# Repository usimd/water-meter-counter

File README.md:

# Inductive water meter counter with S0 interface for GSB-8 meters

This is a custom water meter counter project to get an interface to analog water meter readings
for subsequent usage in Homeassistant. The project is outputting its readings via a generic S0
interface, though, to enable other use cases as well.

It features a custom 3D-printable model to snap on to the GSB-8 meter that houses the PCB. The
software doing the actual work is located in the [`firmware`](./firmware) folder. Since it is
based on a Microchip PIC controller, it requires the respective infrastructure to build.

Bundled assets are available as GitHub releases, created by CI for every `v*` tag:

- firmware `*-production.hex` (normal use) and `*-debug.hex` (additionally prints every sample
  on the UART, 9600 8N1, for re-tuning), plus the matching `.elf` files,
- Gerber and drill files (`*-gerbers.zip`), BOM and pick-and-place CSVs, schematic PDF,
- 3MF file and FreeCAD model of the housing.
- license texts (`LICENSE-*.txt`).

To build the firmware locally, open `firmware` with the MPLAB extensions for VS Code, or run
`cmake --preset water_meter_counter_default_conf -S firmware/cmake/water-meter-counter/default`
followed by `cmake --build firmware/_build/water-meter-counter/default`. Each build writes both
`firmware/out/water-meter-counter/default.hex` (production) and `default-debug.hex`; the debug
variant is defined in `firmware/cmake/water-meter-counter/default/user.cmake`.

## How the firmware counts

The meter's half-disc turns once per litre and passes two LC tanks, A and B. Every ~70 ms the
PIC18F25K80 wakes from Sleep, rings both tanks and sleeps again until the watchdog wakes it.

Both tanks are read the same way. After the tank is excited and released, comparator 1 compares
its sense pin with CVREF, and its output gates Timer1. Timer1 adds up how long the ring-down spends
below the threshold. This is timed in hardware, so it reads the same after a wake from Sleep.

- **Tank B** (CVREF 17/32 VDD) alternates once per revolution between a rest level and a higher
  pass level (~107 and ~134 ticks of 0.25 µs on the bench). Each pass is one litre. The rest
  level is tracked down quickly but up only slowly, so at a slow trickle the baseline cannot
  follow B's ramp into the pass.
- **Tank A** (CVREF 16/32 VDD) gives the direction. Its level changes in the middle of a B pass:
  A falling across the pass (~70 → ~60 ticks) means forward, rising means reverse.

Each revolution is counted in two half steps of 0.5 L: the B pass, and the rest phase between two
passes. The rest phase is decided like the pass, mirrored: A recovers (rises) over a forward rest
phase. Where A barely changes outside the pass, the next decided pass corrects the rest half step,
so the total stays two half steps per litre. The halves are not equal in time: the pass covers
about two thirds of a revolution, so the rate derived from single pulses jitters while the volume
is exact.

Each forward half step emits a 100 ms S0 pulse on RB4, so **1 pulse = 0.5 L (2000 pulses/m³)**.
Pulses are queued and kept at least one sample apart. Reverse half steps are counted and have to
be made up by forward ones before pulses resume, so the pulse total follows the net volume.
If B sits in its pass level at power-up, that first pass is skipped while the baseline settles.

The ADC is not used and stays off with its input selector on the unconnected RA0. The pin the
selector points at sources about 2 µA, even with the ADC off. On a 165 kΩ sense node that lifts
the bias by ~0.35 V, more than two comparator steps, which made B unreadable while the selector
sat on it.

Measured at 5 V with the production firmware: ~350 µA idle (no flow) and up to ~5 mA during an
S0 pulse, when the CPU stays awake and the optocoupler LED is on.

## Using it with ESPHome

ESPHome's `pulse_meter` reads the S0 output directly. Replace the pin with the GPIO your S0 line
is wired to. Enable the internal pull-up if the receiving board has no pull-up of its own.

```yaml
sensor:
  - platform: pulse_meter
    name: "Water flow"
    pin:
      number: GPIOxx
      mode:
        input: true
        pullup: true
    internal_filter: 50ms   # pulses are 100 ms long and at least ~170 ms apart
    timeout: 3min           # report 0 L/min after this long without a pulse
    unit_of_measurement: "L/min"
    accuracy_decimals: 1
    filters:
      - multiply: 0.5       # pulses/min -> L/min
      - throttle_average: 60s
    total:
      name: "Water total"
      unit_of_measurement: "m³"
      device_class: water
      state_class: total_increasing
      accuracy_decimals: 4
      filters:
        - multiply: 0.0005  # 1 pulse = 0.5 L
```

Pass and rest halves take different times, so the rate from single pulses jitters. The
`throttle_average` filter smooths this out; the total is unaffected. For the Energy dashboard,
use the total sensor. It restarts at 0 when the ESP reboots, which `total_increasing` handles.

## Lessons learned from rev1

On the first board revision the LC tanks barely rang. After excitation the sense node stayed
almost flat instead of showing the expected multi-cycle ring-down.

**Simulation ruled out the architecture.** The analog front end was modelled in KiCad/ngspice:

- A GPIO charges the 470 µH / 2.2 nF tank through a 470 Ω resistor and a Schottky diode.
- The GPIO release to hi-Z is modelled as a switch.
- The sense node is AC-coupled through 100 pF and biased to VDD/2 by a 330k/330k divider before
  it reaches the comparator.
- Board and pin parasitics are added as small capacitors and large resistors.

The simulation shows a clean ~156 kHz ring-down after the drive pulse ends at 200 µs. Blue is
the drive, green the tank node and purple the biased sense node. Many cycles cross the
comparator's 2.5 V threshold. The topology works, so the problem had to be physical.

**Root cause: copper under the inductors.** Rev1 had a solid GND pour on both layers directly
beneath L1 and L2. The coils' open magnetic field induces eddy currents in that copper. Those
currents load the tanks and destroy their Q. Rev2 adds copper-pour keepouts under and around both
inductors and the sense circuitry, and uses 470 µH coils. On rev2 the tanks ring as expected.

## References

Inspiration:

- [SanglierLab: Capteur sans fil pour compteur d'eau avec Cyble, partie 1 – principe de fonctionnement](https://www.sanglierlab.fr/2022/12/08/capteur-sans-fil-pour-compteur-deau-avec-cyble-partie-1-principe-de-fonctionnement/)

Helpful references:

- [TI TIDA-01228: Low-power water flow measurement with inductive sensing reference design](https://www.ti.com/tool/TIDA-01228)
- [TI TIDU487: Gas or Water Meter with Two LC Sensors](https://www.ti.com/lit/pdf/tidu487)
- [TI TIDA-010050: Ultra-low power water flow measurement for AMR reference design](https://www.ti.com/tool/TIDA-010050)

## License

- Hardware (schematic, PCB, footprints, housing, renders and documentation):
  [CERN-OHL-S-2.0](./LICENSES/CERN-OHL-S-2.0.txt).
- Firmware (`firmware/`) and CI: [Apache-2.0](./LICENSES/Apache-2.0.txt).
- `firmware/mcc_generated_files/` is generated by MPLAB Code Configurator and remains under
  [Microchip's license](./LICENSES/LicenseRef-Microchip-MCC.txt), which only allows its use with
  Microchip products. The firmware images contain this code.

Per-file details follow the [REUSE](https://reuse.software) specification (SPDX headers and
[`REUSE.toml`](./REUSE.toml)); CI checks compliance with `reuse lint`.

## AISLER discount

This project has been prototyped at [AISLER](https://aisler.net/p/BFTGUQNT). You can instantly
order as well by clicking on the badge at the top.

In case you want to build this (or any other project) at AISLER, here's a 10€ discount code:
`MakeInEurope-ZDCTN`

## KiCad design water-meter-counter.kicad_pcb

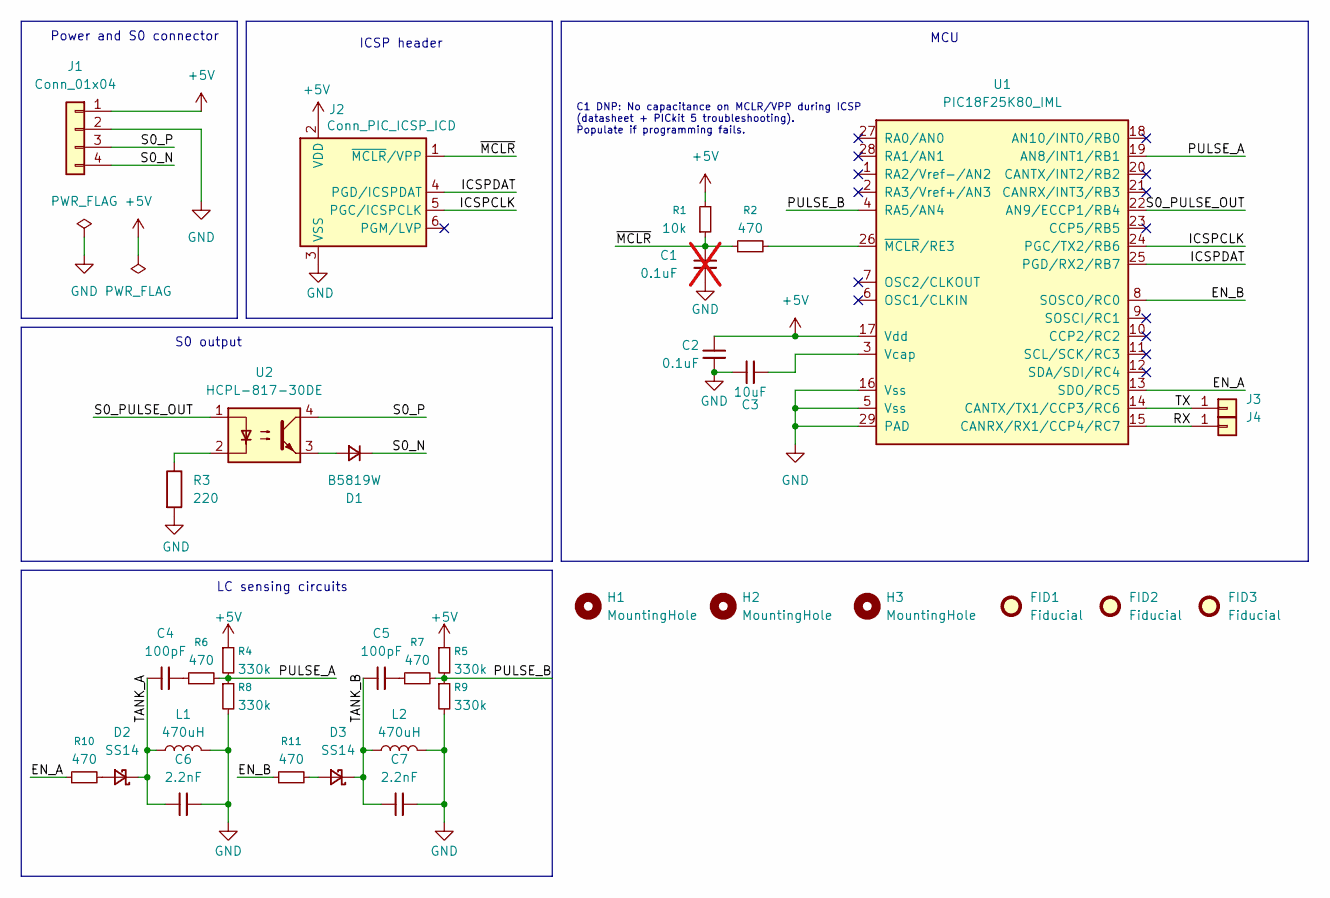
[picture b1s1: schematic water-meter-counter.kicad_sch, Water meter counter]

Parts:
C1: 0.1uF; C_0603_1608Metric; MPN 06035C104JAT2A; not fitted
C2: 0.1uF; C_0603_1608Metric; MPN 06035C104JAT2A
C3: 10uF; C_0603_1608Metric; MPN GRM188R61E106KA73D
C4, C5: 100pF; C_0603_1608Metric; MPN C0603C101J5GACTU
C6, C7: 2.2nF; C_0603_1608Metric; MPN C0603C222J5GACTU
D1: B5819W; D_SOD-123; MPN B5819W
D2, D3: SS14; D_SOD-123F; MPN SS14MH
FID1, FID2, FID3: Fiducial; Fiducial_1mm_Mask3mm
H1, H2, H3: MountingHole; MountingHole_2.2mm_M2_ISO7380
J1: Conn_01x04; JST_XH_S4B-XH-A_1x04_P2.50mm_Horizontal; MPN S4B-XH-A(LF)(SN)
J2: Conn_PIC_ICSP_ICD; PinHeader_1x06_P1.27mm_Vertical
J3, J4: Conn_01x01; TestPoint_Keystone_5000-5004_Miniature
L1, L2: 470uH; L_Radial_D4.80mm_P2.50mm_Fastron_05HCP; MPN 05HCP-471K-51
R1: 10k; R_0603_1608Metric; MPN ESR03EZPJ103
R2, R6, R7, R10, R11: 470; R_0603_1608Metric; MPN RC0603FR-07470RL
R3: 220; R_0805_2012Metric; MPN RC0805FR-07220RL
R4, R5, R8, R9: 330k; R_0603_1608Metric; MPN RC0603FR-07330KL
U1: PIC18F25K80_IML; QFN-28-1EP_6x6mm_P0.65mm_EP4.25x4.25mm; MPN PIC18F25K80-I/MM
U2: HCPL-817-30DE; SSO-4_6.7x5.1mm_P2.54mm_Clearance8mm; MPN HCPL-817-30DE

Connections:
+5V: C2.1, J1.1, J2.2 (VDD), R1.2, R4.1, R5.1, U1.17 (Vdd)
/EN_A: R10.1, U1.13 (SDO/RC5)
/EN_B: R11.1, U1.8 (SOSCO/RC0)
/ICSPCLK: J2.5 (PGC/ICSPCLK), U1.24 (PGC/TX2/RB6)
/ICSPDAT: J2.4 (PGD/ICSPDAT), U1.25 (PGD/RX2/RB7)
/PULSE_A: R4.2, R6.2, R8.1, U1.19 (AN8/INT1/RB1)
/PULSE_B: R5.2, R7.2, R9.1, U1.4 (RA5/AN4)
/RX: J4.1 (Pin_1_1), U1.15 (CANRX/RX1/CCP4/RC7)
/S0_N: D1.1 (K), J1.4
/S0_P: J1.3, U2.4
/S0_PULSE_OUT: U1.22 (AN9/ECCP1/RB4), U2.1
/TANK_A: C4.1, C6.1, D2.1 (K), L1.1
/TANK_B: C5.1, C7.1, D3.1 (K), L2.1
/TX: J3.1 (Pin_1_1), U1.14 (CANTX/TX1/CCP3/RC6)
/~MCLR: C1.1, J2.1 (~MCLR/VPP), R1.1, R2.1
GND: C1.2, C2.2, C3.1, C6.2, C7.2, J1.2, J2.3 (VSS), L1.2, L2.2, R3.2, R8.2, R9.2, U1.5 (Vss), U1.16 (Vss), U1.29 (PAD)
unnamed: C4.2, R6.1
unnamed: C5.2, R7.1
unnamed: D1.2 (A), U2.3
unnamed: D2.2 (A), R10.2
unnamed: D3.2 (A), R11.2
unnamed: R3.1, U2.2
unnamed: C3.2, U1.3 (Vcap)
unnamed: R2.2, U1.26 (~MCLR/RE3)

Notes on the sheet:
LC sensing circuits
MCU
ICSP header
C1 DNP: No capacitance on MCLR/VPP during ICSP (datasheet + PICkit 5 troubleshooting). Populate if programming fails.
Power and S0 connector
S0 output

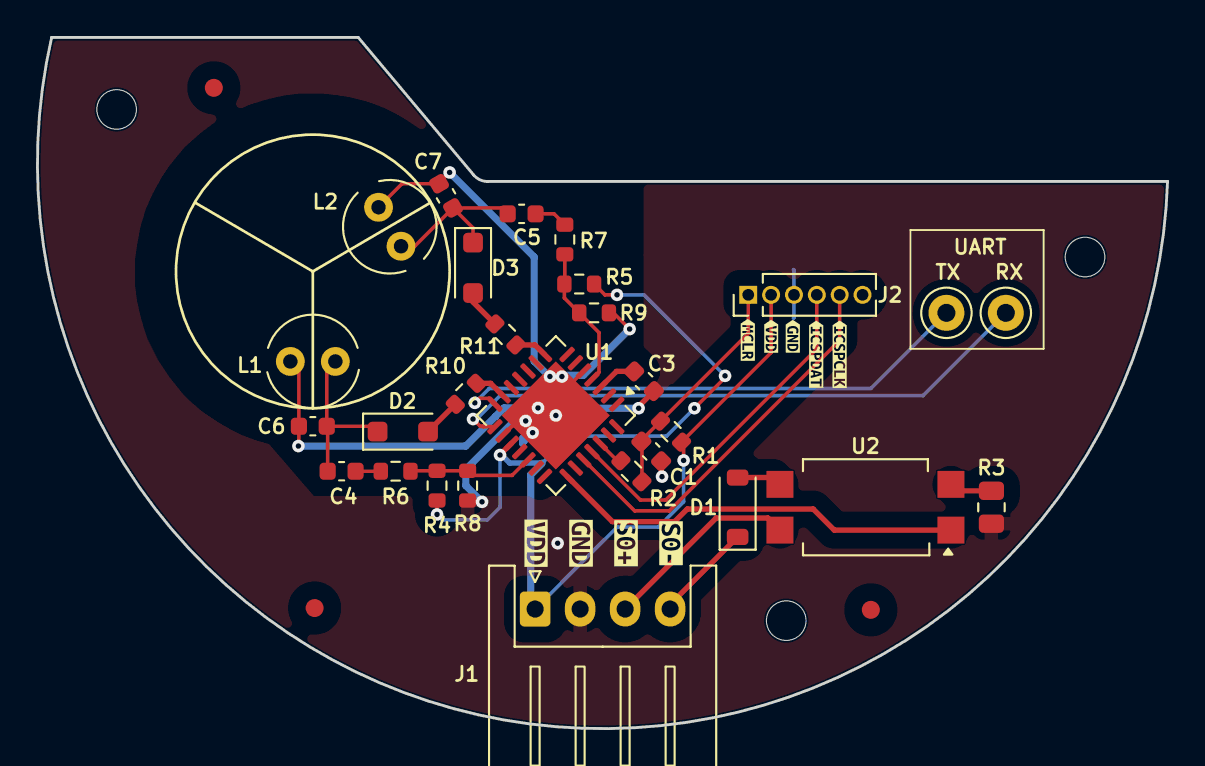
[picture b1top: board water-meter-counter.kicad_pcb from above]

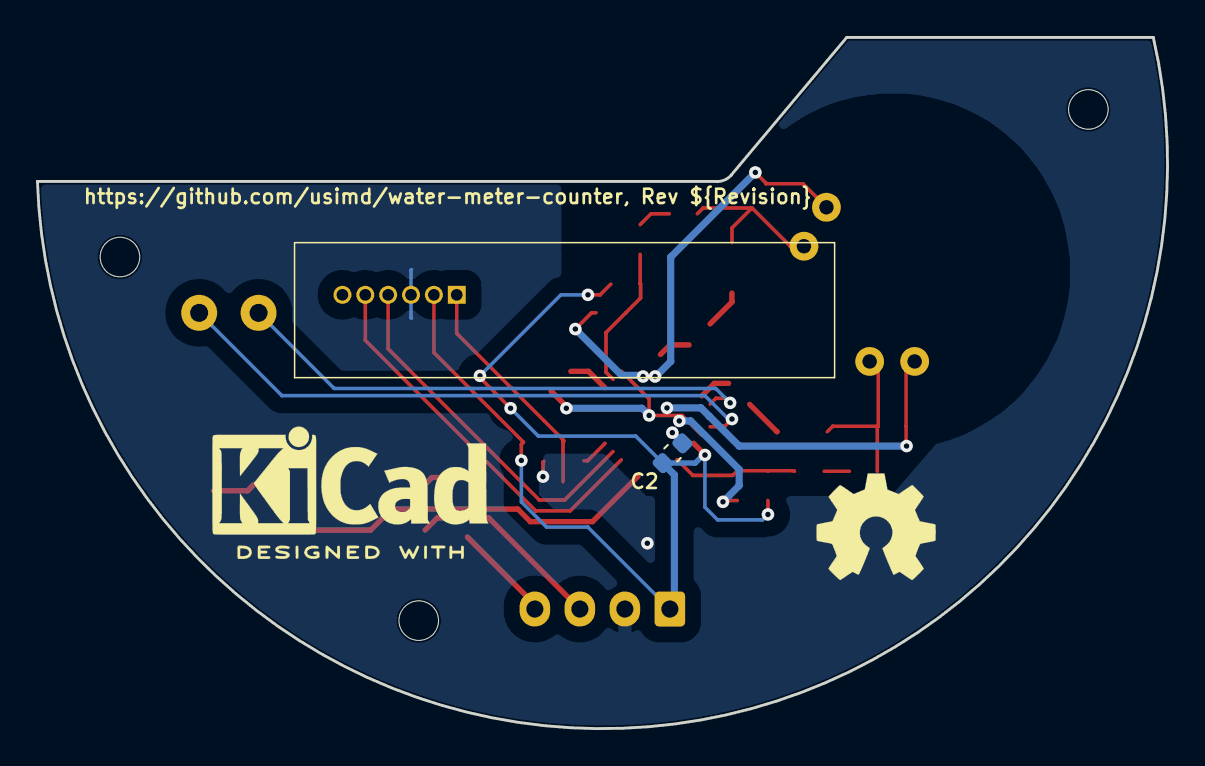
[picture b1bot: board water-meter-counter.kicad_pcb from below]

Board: 2 copper layers, 62.8 x 38.4 mm, 46 parts (3 on the bottom side), 24 nets.

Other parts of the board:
LOGO1: OSHW-Symbol_6.7x6mm_SilkScreen
LOGO2: KiCad-Logo2_6mm_SilkScreen
kibuzzard-69E7705E: G***; kibuzzard-69E7705E
kibuzzard-69E7706B: G***; kibuzzard-69E7706B
kibuzzard-69E77065: G***; kibuzzard-69E77065
kibuzzard-69E77073: G***; kibuzzard-69E77073
kibuzzard-6924F10E: G***; kibuzzard-6924F10E
kibuzzard-6924F13D: G***; kibuzzard-6924F13D
kibuzzard-6924F128: G***; kibuzzard-6924F128
kibuzzard-6945164F: G***; kibuzzard-6945164F
kibuzzard-69451647: G***; kibuzzard-69451647

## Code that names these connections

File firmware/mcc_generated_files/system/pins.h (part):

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// get/set RA5 aliases
#define IO_RA5_TRIS                 TRISAbits.TRISA5
#define IO_RA5_LAT                  LATAbits.LATA5
#define IO_RA5_PORT                 PORTAbits.RA5
#define IO_RA5_WPU                  WPUAbits.
#define IO_RA5_OD                   ODCONAbits.
#define IO_RA5_ANS                  ANSELAbits.ANSEL4
#define IO_RA5_SetHigh()            do { LATAbits.LATA5 = 1; } while(0)
#define IO_RA5_SetLow()             do { LATAbits.LATA5 = 0; } while(0)
#define IO_RA5_Toggle()             do { LATAbits.LATA5 = ~LATAbits.LATA5; } while(0)
#define IO_RA5_GetValue()           PORTAbits.RA5
#define IO_RA5_SetDigitalInput()    do { TRISAbits.TRISA5 = 1; } while(0)
#define IO_RA5_SetDigitalOutput()   do { TRISAbits.TRISA5 = 0; } while(0)
#define IO_RA5_SetPullup()          do { WPUAbits. = 1; } while(0)
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// get/set RB1 aliases
#define IO_RB1_TRIS                 TRISBbits.TRISB1
#define IO_RB1_LAT                  LATBbits.LATB1
#define IO_RB1_PORT                 PORTBbits.RB1
#define IO_RB1_WPU                  WPUBbits.WPUB1
#define IO_RB1_OD                   ODCONBbits.
#define IO_RB1_ANS                  ANSELBbits.ANSEL8
#define IO_RB1_SetHigh()            do { LATBbits.LATB1 = 1; } while(0)
#define IO_RB1_SetLow()             do { LATBbits.LATB1 = 0; } while(0)
#define IO_RB1_Toggle()             do { LATBbits.LATB1 = ~LATBbits.LATB1; } while(0)
#define IO_RB1_GetValue()           PORTBbits.RB1
#define IO_RB1_SetDigitalInput()    do { TRISBbits.TRISB1 = 1; } while(0)
#define IO_RB1_SetDigitalOutput()   do { TRISBbits.TRISB1 = 0; } while(0)
#define IO_RB1_SetPullup()          do { WPUBbits.WPUB1 = 1; } while(0)
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// get/set RB4 aliases
#define S0_TRIS                 TRISBbits.TRISB4
#define S0_LAT                  LATBbits.LATB4
#define S0_PORT                 PORTBbits.RB4
#define S0_WPU                  WPUBbits.WPUB4
#define S0_OD                   ODCONBbits.
#define S0_ANS                  ANCON1bits.ANSEL9
#define S0_SetHigh()            do { LATBbits.LATB4 = 1; } while(0)
#define S0_SetLow()             do { LATBbits.LATB4 = 0; } while(0)
#define S0_Toggle()             do { LATBbits.LATB4 = ~LATBbits.LATB4; } while(0)
#define S0_GetValue()           PORTBbits.RB4
#define S0_SetDigitalInput()    do { TRISBbits.TRISB4 = 1; } while(0)
#define S0_SetDigitalOutput()   do { TRISBbits.TRISB4 = 0; } while(0)
#define S0_SetPullup()          do { WPUBbits.WPUB4 = 1; } while(0)
#define S0_ResetPullup()        do { WPUBbits.WPUB4 = 0; } while(0)
// RB4 has no per-pin open-drain control; ANSEL9 uses 1=analog, 0=digital
#define S0_SetPushPull()        do { } while(0)  // No ODCONB bit for RB4
#define S0_SetOpenDrain()       do { } while(0)  // No ODCONB bit for RB4
#define S0_SetAnalogMode()      do { ANCON1bits.ANSEL9 = 1; } while(0)
#define S0_SetDigitalMode()     do { ANCON1bits.ANSEL9 = 0; } while(0)

// get/set RC0 aliases
#define LCB_TRIS                 TRISCbits.TRISC0
#define LCB_LAT                  LATCbits.LATC0
#define LCB_PORT                 PORTCbits.RC0
// RC0 has no WPU, ODCON, or ANSEL bits (SOSC pins are special)
// These macros are intentionally left incomplete - do not use them
#define LCB_SetHigh()            do { LATCbits.LATC0 = 1; } while(0)
#define LCB_SetLow()             do { LATCbits.LATC0 = 0; } while(0)
#define LCB_Toggle()             do { LATCbits.LATC0 = ~LATCbits.LATC0; } while(0)
#define LCB_GetValue()           PORTCbits.RC0
#define LCB_SetDigitalInput()    do { TRISCbits.TRISC0 = 1; } while(0)
#define LCB_SetDigitalOutput()   do { TRISCbits.TRISC0 = 0; } while(0)
// RC0 has no WPU, ODCON, or ANSEL bits - these are no-ops
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// get/set RC5 aliases
#define LCA_TRIS                 TRISCbits.TRISC5
#define LCA_LAT                  LATCbits.LATC5
#define LCA_PORT                 PORTCbits.RC5
// RC5 has no WPU, ODCON, or ANSEL bits
// These macros are intentionally left incomplete - do not use them
#define LCA_SetHigh()            do { LATCbits.LATC5 = 1; } while(0)
#define LCA_SetLow()             do { LATCbits.LATC5 = 0; } while(0)
#define LCA_Toggle()             do { LATCbits.LATC5 = ~LATCbits.LATC5; } while(0)
#define LCA_GetValue()           PORTCbits.RC5
#define LCA_SetDigitalInput()    do { TRISCbits.TRISC5 = 1; } while(0)
#define LCA_SetDigitalOutput()   do { TRISCbits.TRISC5 = 0; } while(0)
// RC5 has no WPU, ODCON, or ANSEL bits - these are no-ops
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// get/set RC6 aliases
#define IO_RC6_TRIS                 TRISCbits.TRISC6
#define IO_RC6_LAT                  LATCbits.LATC6
#define IO_RC6_PORT                 PORTCbits.RC6
// RC6 has no WPU, ODCON, or ANSEL bits (EUSART TX pin)
// These macros are intentionally left incomplete - do not use them
#define IO_RC6_SetHigh()            do { LATCbits.LATC6 = 1; } while(0)
#define IO_RC6_SetLow()             do { LATCbits.LATC6 = 0; } while(0)
#define IO_RC6_Toggle()             do { LATCbits.LATC6 = ~LATCbits.LATC6; } while(0)
#define IO_RC6_GetValue()           PORTCbits.RC6
#define IO_RC6_SetDigitalInput()    do { TRISCbits.TRISC6 = 1; } while(0)
#define IO_RC6_SetDigitalOutput()   do { TRISCbits.TRISC6 = 0; } while(0)
// RC6 has no WPU, ODCON, or ANSEL bits - these are no-ops
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// get/set RC7 aliases
#define IO_RC7_TRIS                 TRISCbits.TRISC7
#define IO_RC7_LAT                  LATCbits.LATC7
#define IO_RC7_PORT                 PORTCbits.RC7
// RC7 has no WPU, ODCON, or ANSEL bits (EUSART RX pin)
// These macros are intentionally left incomplete - do not use them
#define IO_RC7_SetHigh()            do { LATCbits.LATC7 = 1; } while(0)
#define IO_RC7_SetLow()             do { LATCbits.LATC7 = 0; } while(0)
#define IO_RC7_Toggle()             do { LATCbits.LATC7 = ~LATCbits.LATC7; } while(0)
#define IO_RC7_GetValue()           PORTCbits.RC7
#define IO_RC7_SetDigitalInput()    do { TRISCbits.TRISC7 = 1; } while(0)
#define IO_RC7_SetDigitalOutput()   do { TRISCbits.TRISC7 = 0; } while(0)
// RC7 has no WPU, ODCON, or ANSEL bits - these are no-ops
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
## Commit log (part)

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2025-12-19 First draft of firmware
2025-12-19 Include CMake presets
2025-12-19 Fix CMake generation
2025-12-19 Set CMake generator to Ninja
2025-12-19 Try CMake generation without preset
2026-01-21 Fix RC0 GPIO, improve S0 resolution to 0.5L/pulse, fix MCC pin macros
    - config_bits.c: Set SOSCSEL=DIG to release RC0/RC1 from SOSC mode
    - config_bits.c: Add comment that XINST=OFF is required for XC8
    - main.c: Add runtime SOSCGO=0, T1OSCEN=0, SOSCEN=0 to fully disable SOSC
    - main.c: Update comments for 0.5L/pulse resolution and correct pin assignments
    - water_meter.c: Re-enable dual LC tank sensing (LCB was disabled for debugging)
    - water_meter.c: Generate S0 pulse on each LC state transition (was every 2)
2026-04-28 Prepare Rev2

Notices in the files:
README.md:
Hardware: CERN-OHL-S-2.0
